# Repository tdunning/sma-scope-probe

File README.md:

# SMA Oscilloscope Probes

This project has a hardware design with parts ordering links for an oscilloscope probe that terminates in an SMA connector. This is useful when you want a solid, long-lasting connection for making measurements.

# How Oscilloscope Probes Work

A standard 10x oscilloscope works to decrease the impact of oscilloscope on the circuit it is measuring by 
using a 10:1 resistive divider right at the probe tip that increases the impedance and thus the disturbance on the measured circuit.

If, however, you just use a resistive divider, the results are not very good. What happens is that the capacitance 
of the oscilloscope input combined with the capacitance of the cable to the oscilloscope forms a low pass filter
when combined with the resistive divider. Further more, it forms a *very* low pass divider because the capacitance
of the scope is typically about 15pF plus as much as 100pF from the cable and the resistance of the divider is 9MΩ from the probe so we have a time constant of considerably more than 100µ seconds which we can't get more than a few kHz
bandwidth through to measure.

The effective circuit looks like this:

To solve this problem of low bandwidth, the traditional solution is to put a bit of capacitance in parallel with
the first resistor (the 9MΩ one). That causes the impedance of the two resistance+capacitor combinations to be
proportional even to very high frequencies. Looks a bit like this:

Traditionally, there is a variable capacitance added in parallel with the oscilloscope so that the balance between
the two parts of the divider can be set very precisely. That adjustable capacitance is usually put near the 
oscilloscope and the input resistance and corresponding capacitor are put in the oscilloscope probe itself. A big 
reason for that, however, is mechanical and is done to avoid the weight in the probe and to avoid knocking an adjustable
capacitor around so much.

# What's Different Here?

It is pretty common that I am working on a project and I want to leave my 10x probes connected to an electronic circuit project. This can be for 10 minutes while I mess with something in the circuit or it might be for 10 weeks, especially if I am working on the software part of a project, but need to check periodically on the effect on the hardware side.

Leaving conventional scope probes connected is often a problem because they are big and often slip out of place. They're great when you are moving from point to point in the design, but when you want something really stable they aren't nearly as good.

Some times, I can design in some 50 ohm outputs that can be semi-permanently connected by setting the oscilloscope to 50ohm termination, but then the question is what happens if I disconnect the oscilloscope? Or if my scope doesn't have a 50ohm termination option? Or if the circuit won't be happy being loaded so heavily.

What I really want in these moments is a high impedance 10x probe that has an SMA connector instead of a traditional scope probe. Because the weight at the probe end doesn't really matter, we can build all of the compensation and tuning circuitry onto a single small board. That board has the following circuit:

This circuit has two resistors to create the desired 9MΩ because the available thick-film chip resistor values can get 
closer to the desired value this way. Similarly, there are two parallel capacitors so that the different capacitors can be combined to get very close to the required value depending on the length of cable you need and such. This circuit is laid out onto a small (21.5 x 13.0 mm) board with SMA connectors.

This directory contains the KiCAD layout for this probe. This circuit has a very conventional 10x divider with capacitors that allow you to tune the compensation on the probe for flat response. There is no provision for calibration, but the specified resistors should be within 1%.

You can order [the board from OSH Park](https://oshpark.com/shared_projects/0noho4Gm).

# Building the Previous Version

This section describes building the older two-part version of the circuit. It will be replaced by a new section when the updated boards and parts arrive.

The circuit diagram above is all fine and good with respect to the capacitance of the input of the 
oscilloscope, but it leaves out the crucial factor of the capacitance of the coax between the two parts of the attenuator. This cable acts like a capacitance because it is short compared to the wavelengths of interest (less than 1m versus 3m). The spec for RG-316 which is commonly used with SMA connectors is 100±5pF / m. In my case, I am interested in is 50cm long so I can expect about 50pF extra. With the 14pF of the scope itself and the 3-10pF of the variable capacitor, that's 66-74pF which needs compensated. This means that we need about 6.5-7.5pF, give or take, instead of 2pF at the probe end. The other effect of this additional capacitance is that the variable capacitor really doesn't have as much bite as we would like so the capacitance at the probe end has to be in a very narrow range. It would be better to use a trimmer with higher capacitance in the next version.

In building the first version of the system, I needed about 8pF on the probe unit to give the trimmer capacitor enough swing to tune the response. With only a single 0805 pad to work with, I removed the SMD capacity from the board and used two disk capacitors. In future versions, I will set up more than one footprint on the board to allow tweaks like this.

One other improvement for future versions is that I would prefer to have two footprints for the resistors since it is easy to get 4.99 and 4.02 MΩ resistors but in larger values, the closest I could get for the divider resistor was 9.1 ΜΩ.

Once you have found an appropriate capacitance, you should be able to use the trimmer to see a waveform like this with a normal calibration signal.

# Parts

This list at Digikey has [all of the passive components](https://www.digikey.com/en/mylists/list/1PMQ8QBF5N) except for the SMA connectors which are a bit expensive from primary parts vendors like Digikey. You can pick these up all over the place for <$1 per connector. See the following items at Amazon, for instance:

* https://www.amazon.com/Superbat-Connectors-Coaxial-Connector-Vertical/dp/B09V6ZY1PH
* https://www.amazon.com/QMseller-Launch-Straight-Connector-Adapter/dp/B07GXSN7VS
* https://www.amazon.com/bnafes-Straight-Connector-Coaxial-Adapter/dp/B09N1RBBFX

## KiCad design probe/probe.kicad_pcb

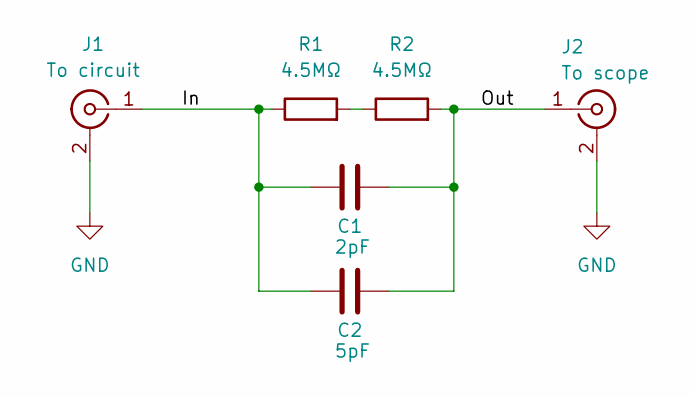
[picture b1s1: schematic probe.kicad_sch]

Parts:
C1: 2pF; C_0805_2012Metric
C2: 5pF; C_0805_2012Metric
J1: To circuit; SMA_Samtec_SMA-J-P-H-ST-EM1_EdgeMount
J2: To scope; SMA_Samtec_SMA-J-P-H-ST-EM1_EdgeMount
R1, R2: 4.5MΩ; R_0805_2012Metric_Pad1.20x1.40mm_HandSolder

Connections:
/In: C1.1, C2.1, J1.1 (In), R1.1
/Out: C1.2, C2.2, J2.1 (In), R2.2; also elsewhere on the board
GND: J1.2 (Ext), J2.2 (Ext); also elsewhere on the board
unnamed: R1.2, R2.1

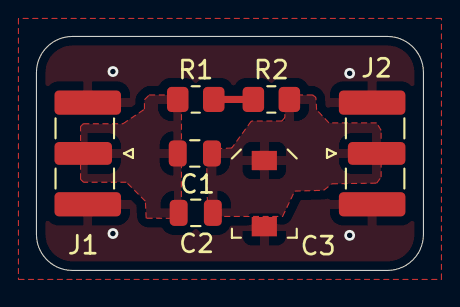
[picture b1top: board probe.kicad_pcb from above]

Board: 2 copper layers, 21.5 x 13.0 mm, 7 parts (0 on the bottom side), 4 nets.

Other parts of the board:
C3: 8-30pF; C_Trimmer_Sprague-Goodman_SGC3

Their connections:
/Out: C3.1; also elsewhere on the board
GND: C3.2; also elsewhere on the board

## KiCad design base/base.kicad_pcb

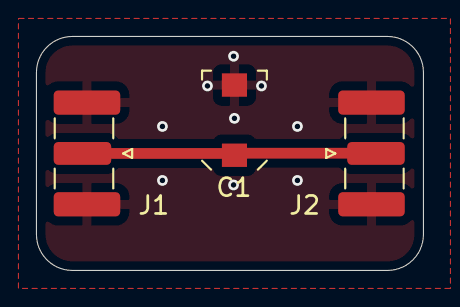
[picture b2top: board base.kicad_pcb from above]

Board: 2 copper layers, 21.5 x 13.0 mm, 3 parts (0 on the bottom side), 2 nets.

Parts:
C1: C_Trim; C_Trimmer_Sprague-Goodman_SGC3
J1, J2: Conn_Coaxial; SMA_Samtec_SMA-J-P-H-ST-EM1_EdgeMount

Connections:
GND: C1.2, J1.2 (Ext), J2.2 (Ext)
unnamed: C1.1, J1.1 (In), J2.1 (In)

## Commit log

2025-12-21 Update README.md with a picture
2025-12-21 Include OSH Park ordering links in README
    Added links to order circuit boards from OSH Park.
2025-12-21 Update OSH Park link for the probe
2025-12-21 Add MIT License to the project
2025-12-21 Add parts section with component links
    Added a section for parts with links to passive components and SMA connectors.
2026-01-29 Updated to account for lead capacitance.
2026-01-31 Combined both boards into single probe board
2026-01-31 Update based on first constructed version
2026-01-31 Updated README with improvement ideas
2026-01-31 Updated to describe next revision of the project.
2026-01-31 Latest PCB design
2026-01-31 Cleanup for tagging
2026-01-31 Minor clarification
2026-01-31 Removing obsolete board Remove reference to second board
2026-04-08 Added clarifying note to schematic.
